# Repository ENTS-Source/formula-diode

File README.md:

# led-race
Race each other on an LED strip, using an ESP8266

## Arduino libraries

* Regexp
* AsyncHTTPRequest_Generic
* ESP8266WiFi
* WiFiManager

## Running scoreboard

`npm install && npm start` in `pi-scoreboard`

Screenshot:

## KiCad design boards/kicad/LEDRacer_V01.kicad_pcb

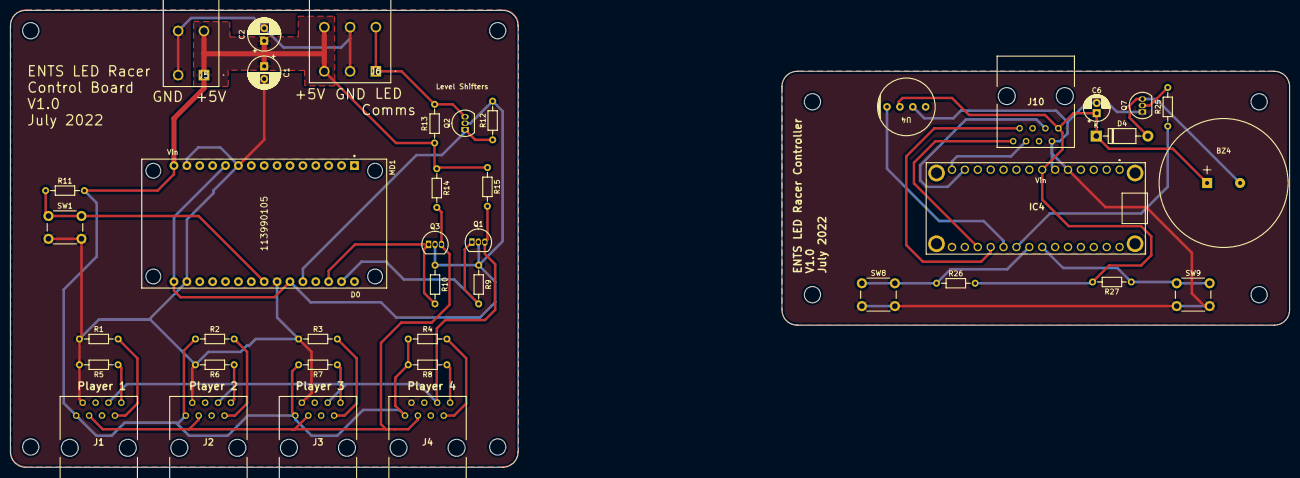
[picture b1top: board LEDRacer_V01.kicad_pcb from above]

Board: 2 copper layers, 251.9 x 89.9 mm, 40 parts (0 on the bottom side), 28 nets.

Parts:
BZ4: Buzzer; WT1209
C1, C2: C_Polarized; CP_Radial_D6.3mm_P2.50mm
C6: C_Polarized; CP_Radial_D5.0mm_P2.00mm
D4: D; D_DO-41_SOD81_P10.16mm_Horizontal
IC4: 2590
J1, J2, J3, J4, J10: 54601-908WPLF; 54601908WPLF
J5: 1017491
J6: 1017492
MD1: 113990105; Seeed_Studio-113990105-MFG
Q1, Q2, Q3: TN0104N3-G; TO-92_Inline
Q7: Q_NPN_EBC; TO-92_Inline
R1, R2, R3, R4, R5, R6, R7, R8: 1k; R_Axial_DIN0204_L3.6mm_D1.6mm_P7.62mm_Horizontal
R9, R10, R14, R15: 4.7K; R_Axial_DIN0204_L3.6mm_D1.6mm_P7.62mm_Horizontal
R11, R12, R13, R26, R27: 4.7k; R_Axial_DIN0204_L3.6mm_D1.6mm_P7.62mm_Horizontal
R25: 1.5k; R_Axial_DIN0204_L3.6mm_D1.6mm_P7.62mm_Horizontal
SW1, SW8, SW9: SW_Push; SW_PUSH_6mm
U4: COM-12986; COM12986

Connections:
+3V3: MD1.11 (3V3), MD1.16 (3V3), MD1.25 (3V3), Q1.2 (G), Q2.2 (G), Q3.2 (G), R9.1, R10.1, R12.2
+5V: BZ4.1 (-), C1.1, C2.1, C6.1, D4.1 (K), IC4.7 (VIN), J1.1, J2.1, J3.1, J4.1, J5.1 (1.1), J5.2 (1.2), J6.5 (3.1), J6.6 (3.2), J10.1, MD1.15 (VIN), R2.1, R4.1, R7.2, R8.2, R11.2, R13.2, R14.1, R15.1, R26.2, R27.2, U4.2 (VDD)
/Button: MD1.23 (D5), R11.1, SW1.1
/Controller3/Button_1: IC4.21 (I/O_6), R26.1, SW8.1
/Controller3/Button_2: IC4.22 (I/O_7), R27.1, SW9.1
/Controller3/Buzzer: IC4.20 (I/O_5), R25.1
/Controller3/ID_1: IC4.18 (I/O_3), J10.7
/Controller3/ID_2: IC4.17 (I/O_2), J10.8
/Controller3/LED_Sig: IC4.19 (I/O_4), U4.1 (DIN)
/Controller3/SCL_HV: IC4.14 (A5), J10.6
/Controller3/SDA_HV: IC4.13 (A4), J10.3
/LED_COMM_HV: J6.1 (1.1), J6.2 (1.2), Q2.3 (D), R13.1
/LED_COMM_LV: MD1.26 (D4), Q2.1 (S), R12.1
/SCL_HV: J1.6, J2.6, J3.6, J4.6, Q1.3 (D), R15.2
/SCL_LV: MD1.29 (D1), Q1.1 (S), R9.2
/SDA_HV: J1.3, J2.3, J3.3, J4.3, Q3.3 (D), R14.2
/SDA_LV: MD1.28 (D2), Q3.1 (S), R10.2
GND: C1.2, C2.2, C6.2, IC4.5 (GND_1), IC4.6 (GND_2), J1.2, J2.2, J3.2, J4.2, J5.3 (2.1), J5.4 (2.2), J6.3 (2.1), J6.4 (2.2), J10.2, MD1.10 (GND), MD1.14 (GND), MD1.17 (GND), MD1.24 (GND), Q7.1 (E), R1.1, R3.1, R5.2, R6.2, SW1.2, SW8.2, SW9.2, U4.3 (VSS)
unnamed: BZ4.2 (+), D4.2 (A), Q7.3 (C)
unnamed: J1.7, R1.2
unnamed: J1.8, R5.1
unnamed: J2.7, R2.2
unnamed: J2.8, R6.1
unnamed: J3.7, R3.2
unnamed: J3.8, R7.1
unnamed: J4.7, R4.2
unnamed: J4.8, R8.1
unnamed: Q7.2 (B), R25.2

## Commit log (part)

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2022-04-02 Add early game structures; traffic light
2022-04-10 Initial game physics
2022-04-11 Initial rework of engine
2022-04-11 Move physics back into PlayerController
2022-04-11 Fix height map not working at all
2022-04-13 Add support for laps
2022-04-13 Add networking layer (unused)
2022-04-13 Use WifiManager
2022-04-13 Remove debug
2022-04-14 Adjust params from testing
2022-04-15 Add early config variables
2022-04-15 Adjust traffic light colours
2022-04-16 Add basics for a controller board
2022-05-23 Move controllers to I2C bus
2022-05-24 Start early scoreboard comms
2022-06-08 Try to use MQTT for server
2022-06-30 Create electron app
2022-06-30 Set up the window
2022-06-30 UI Mockup for scoreboard
2022-07-09 Project cleanup
2022-07-10 Early new-networking code (async http)
2022-07-10 Restructure web app a bit
2022-07-12 Convert button class to a proper struct
2022-07-13 Add circuit board stuff
2022-07-13 Embrace functional programming
2022-07-13 Make the code run again and add debugging
    Outstanding issues: scoreboard IP is getting corrupted (use cstrings?) and it crashes on game end.
2022-07-14 Add http debug script (temporary)
2022-07-14 List known-required libs in readme
2022-07-14 Fix traffic lights
2022-07-14 Try to use mostly cstrings
2022-07-14 More cstring stuff
2022-07-14 Try to use a request pool
2022-07-14 Fix overrun on LEDs array (memory corruption)
2022-07-14 Remove debugging
2022-07-15 Wire up the scoreboard
2022-07-15 Remove httpdebug
2022-07-15 Update design
2022-07-15 Fix game state issues (race conditions on requests)
2022-07-16 Ping i2c to try and reduce disconnects
2022-07-16 Adjust/cleanup defaults
2022-07-16 Adjust traffic light green state
2022-07-16 Add a screensaver
2022-07-16 Reduce impact of renders on app loop when scaled up to 300 LEDs
2022-07-16 Hook up automated state to the scoreboard properly
2022-07-16 Scan for i2c during screensaver
2022-07-20 Initial game adjustments
2022-07-20 Add gravity
2022-09-22 Disable motor control
2022-09-22 Fix ID LED for boards
2022-09-22 Add track specific values and speed boosts
2025-07-18 2025 changes
